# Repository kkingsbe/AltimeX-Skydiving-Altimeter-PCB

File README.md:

# AltimeX

This repo contains the PCB files for an open-source ColorAlti analog that I created, which can be made for about $30. Sadly, the programmer cable costs anywhere from $60-$120, however if you need yours programmed you can reach out to me and we can work something out (I have one).

This is still an active work in progress. A LiPo with a capacity of at least 250mAh should be fine since the current draw of the board is minimal. The CAD files for an enclosure that can fit in the audible pocket on helmets will be up soon once tested.

## Bill of Materials
|Part            |Part Number            |Price (per item)|Amount|Link|
|----------------|-----------------------|----------------|------|----|
|MCU             |STM32F103              |$6.66           |1     |[Click Here](https://www.digikey.com/en/products/detail/stmicroelectronics/STM32F103C8T6/1646338)|
|LED Strip       |WS2813B                |$15.00          |1     |[Click Here](https://www.amazon.com/LOAMLIN-Individually-Addressable-144Pixels-Waterproof/dp/B0BDRCQWWQ/ref=sr_1_30_sspa?crid=3CKX9YASAYWQJ&keywords=ws2813b%2Bled%2Bstrip%2Bhigh%2Bdensity&qid=1681772673&sprefix=ws2813b%2Bled%2Bstrip%2Bhigh%2Bdensity%2Caps%2C69&sr=8-30-spons&spLa=ZW5jcnlwdGVkUXVhbGlmaWVyPUEyUUZPR0xCU1BTRFlNJmVuY3J5cHRlZElkPUEwNDg5NDI1TTdWTUJPUDY0NUJGJmVuY3J5cHRlZEFkSWQ9QTAzMjEyNTgyOTUyUFVVTVlURDdKJndpZGdldE5hbWU9c3BfbXRmJmFjdGlvbj1jbGlja1JlZGlyZWN0JmRvTm90TG9nQ2xpY2s9dHJ1ZQ&th=1)|
|Boost Converter |RP400N501A-TR-FE       |$1.48           |1     |[Click Here](https://www.digikey.com/en/products/detail/nisshinbo-micro-devices-inc/RP400N501A-TR-FE/10244946?s=N4IgTCBcDaIE4AcAsAGFA7ArCgjAQxAF0BfIA)|
|Linear Regulator|LD1117S33TR            |$0.66           |1     |[Click Here](https://www.digikey.com/en/products/detail/stmicroelectronics/LD1117S33TR/585766?s=N4IgTCBcDaIDYBMCMKDsBnAzJgLgJxAF0BfIA)|
|Schottky Diode  |RSX101MM-30TFTR        |$0.45           |1     |[Click Here](https://www.digikey.com/en/products/detail/rohm-semiconductor/RSX101MM-30TFTR/9748173)|
|10uh Inductor   |ASPI-0630LR-100M-T15   |$0.83           |1     |[Click Here](https://www.digikey.com/en/products/detail/abracon-llc/ASPI-0630LR-100M-T15/3059602?s=N4IgTCBcDaIIYGcAOBLAtABgGwGYMBsAnNARgwwFsQBdAXyA)|
|10uF Capactior  |                       |$0.25           |3     |[Click Here](https://www.digikey.com/en/products/detail/murata-electronics/GRM21BR61E106KA73L/2334874)|
|4.7uF Capacitor |                       |$0.10           |1     |[Click Here](https://www.digikey.com/en/products/detail/samsung-electro-mechanics/CL21A475KAQNNNE/3886902)|
|100nF Capacitor |                       |$0.10           |7     |[Click Here](https://www.digikey.com/en/products/detail/yageo/CC0805KRX7R9BB104/302874)|
|JTAG Connector  |FTSH-105-01-H-DV-K-P-TR|$5.63           |1     |[Click Here](https://www.digikey.com/en/products/detail/samtec-inc./FTSH-105-01-H-DV-K-P-TR/9594223?utm_adgroup=Rectangular%20Connectors%20-%20Headers%2C%20Male%20Pins&utm_source=google&utm_medium=cpc&utm_campaign=Shopping_Product_Connectors%2C%20Interconnects_NEW&utm_term=&utm_content=Rectangular%20Connectors%20-%20Headers%2C%20Male%20Pins&gclid=Cj0KCQiAx6ugBhCcARIsAGNmMbh4-y1PB26lYnSIvQfyvOCW9n3EWnzOqesUZbafweeNy_JcrjvtJzoaAvwaEALw_wcB)|
|4.7k Resistor   |                       |$0.10           |2     |[Click Here](https://www.digikey.com/en/products/detail/yageo/RC0402JR-074K7L/726477)|
|500 ohm Resistor|                       |$2.64           |1     |[Click Here](https://www.digikey.com/en/products/detail/vishay-dale/TNPU0805500RAZEN00/6615940)|
|1M Resistor     |                       |$0.10           |1     |[Click Here](https://www.digikey.com/en/products/detail/yageo/RC0805FR-071ML/727445)|
|10MHz Resonator |                       |$0.24           |1     |[Click Here](https://www.digikey.com/en/products/detail/yageo/RC0805FR-071ML/727445)|
|SMD LED         |                       |$0.26           |1     |[Click Here](https://www.digikey.com/en/products/detail/liteon/LTST-C191KRKT/386837)|
|Micro USB Port  |                       |$0.46           |1     |[Click Here](https://www.digikey.com/en/products/detail/amphenol-cs-fci/10118193-0001LF/2785388)|
|Baro Sensor     |LPS22HBTR              |$2.13           |1     |[Click Here](https://www.digikey.com/en/products/detail/stmicroelectronics/LPS22HBTR/5799910)|

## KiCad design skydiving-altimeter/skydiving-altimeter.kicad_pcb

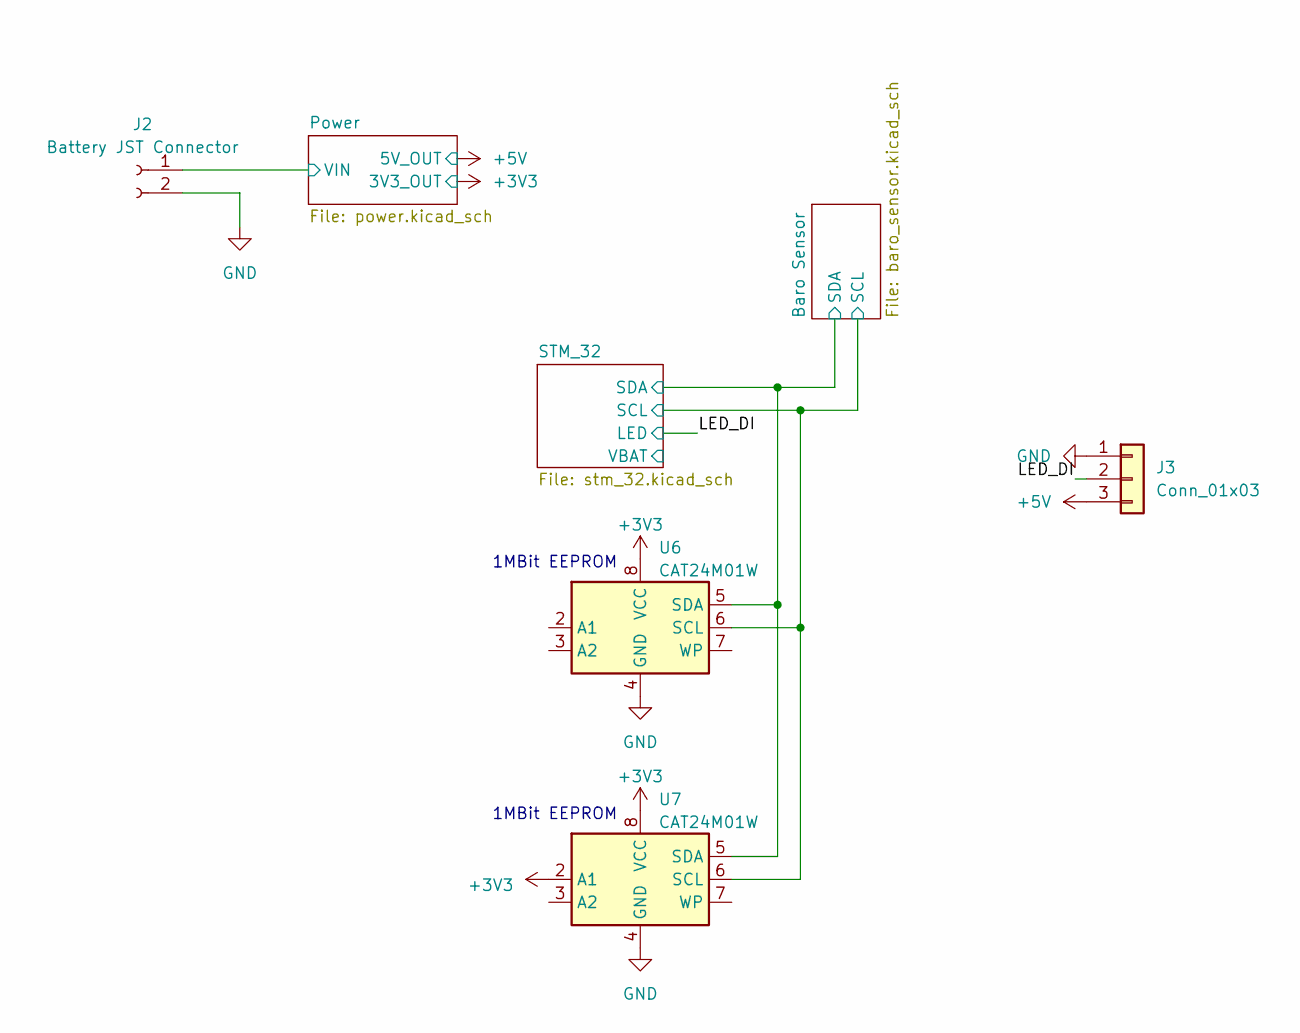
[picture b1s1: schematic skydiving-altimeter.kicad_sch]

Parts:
J2: Battery JST Connector; JST_S2B-PH-K-S(LF)(SN)
J3: Conn_01x03; PinHeader_1x03_P2.54mm_Vertical
U6, U7: CAT24M01W; SOIC-8_3.9x4.9mm_P1.27mm

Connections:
+3V3: U6.8 (VCC), U7.2 (A1), U7.8 (VCC); also elsewhere on the board
+5V: J3.3; also elsewhere on the board
/Baro Sensor/SCL: U6.6 (SCL), U7.6 (SCL); also elsewhere on the board
/Baro Sensor/SDA: U6.5 (SDA), U7.5 (SDA); also elsewhere on the board
/LED_DI: J3.2; also elsewhere on the board
/Power/VIN: J2.1; also elsewhere on the board
GND: J2.2, J3.1, U6.4 (GND), U7.4 (GND); also elsewhere on the board

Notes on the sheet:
1MBit EEPROM

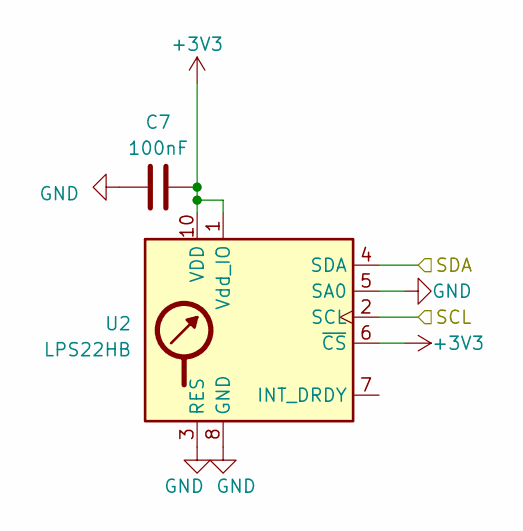
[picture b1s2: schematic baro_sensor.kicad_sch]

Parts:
C7: 100nF; C_0805_2012Metric
U2: LPS22HB; ST_HLGA-10_2x2mm_P0.5mm_LayoutBorder3x2y

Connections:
+3V3: C7.1, U2.1 (Vdd_IO), U2.6 (~CS), U2.10 (VDD); also elsewhere on the board
/Baro Sensor/SCL: U2.2 (SCL); also elsewhere on the board
/Baro Sensor/SDA: U2.4 (SDA); also elsewhere on the board
GND: C7.2, U2.3 (RES), U2.5 (SA0), U2.8 (GND), U2.9 (GND); also elsewhere on the board

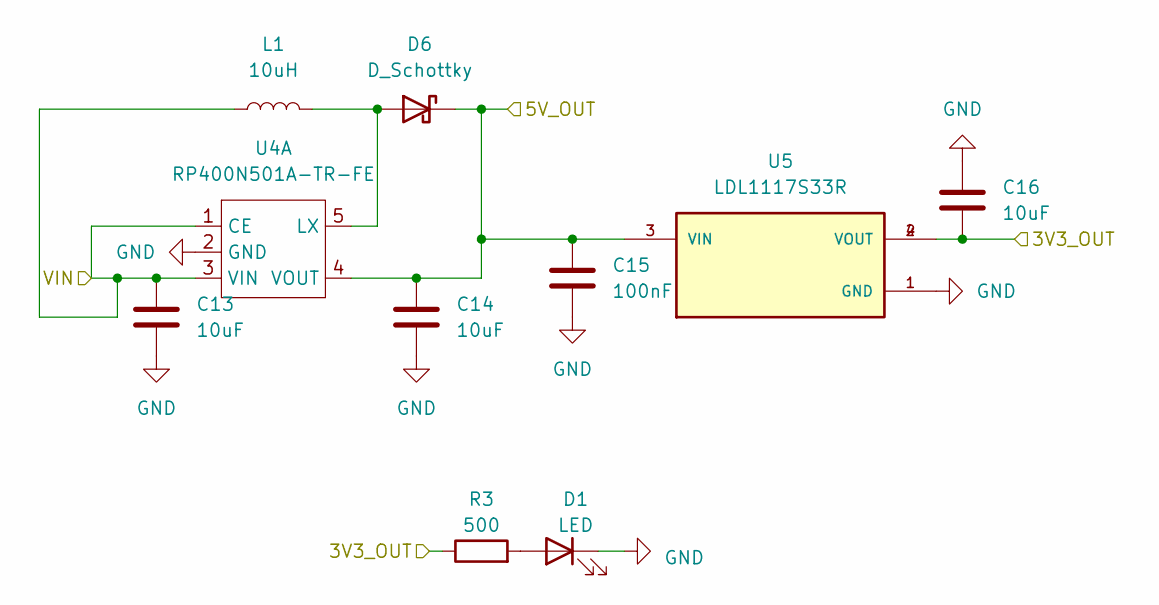
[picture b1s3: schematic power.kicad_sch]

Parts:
C13, C14, C16: 10uF; C_0805_2012Metric
C15: 100nF; C_0805_2012Metric
D1: LED; D_0603_1608Metric
D6: D_Schottky; D_SOD-123F
L1: 10uH; IND_ASPI-0630LR-100M-T15
R3: 500; R_0805_2012Metric
U4: RP400N501A-TR-FE; SOT-23-5
U5: LDL1117S33R; SOT-223; PARTREV 7

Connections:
+3V3: C16.2, R3.1, U5.2 (VOUT), U5.4 (VOUT); also elsewhere on the board
+5V: C14.1, C15.1, D6.1 (K), U4.4 (VOUT), U5.3 (VIN); also elsewhere on the board
/Power/VIN: C13.1, L1.1, U4.1 (CE), U4.3 (VIN); also elsewhere on the board
GND: C13.2, C14.2, C15.2, C16.1, D1.1 (K), U4.2 (GND), U5.1 (GND); also elsewhere on the board
unnamed: D1.2 (A), R3.2
unnamed: D6.2 (A), L1.2, U4.5 (LX)

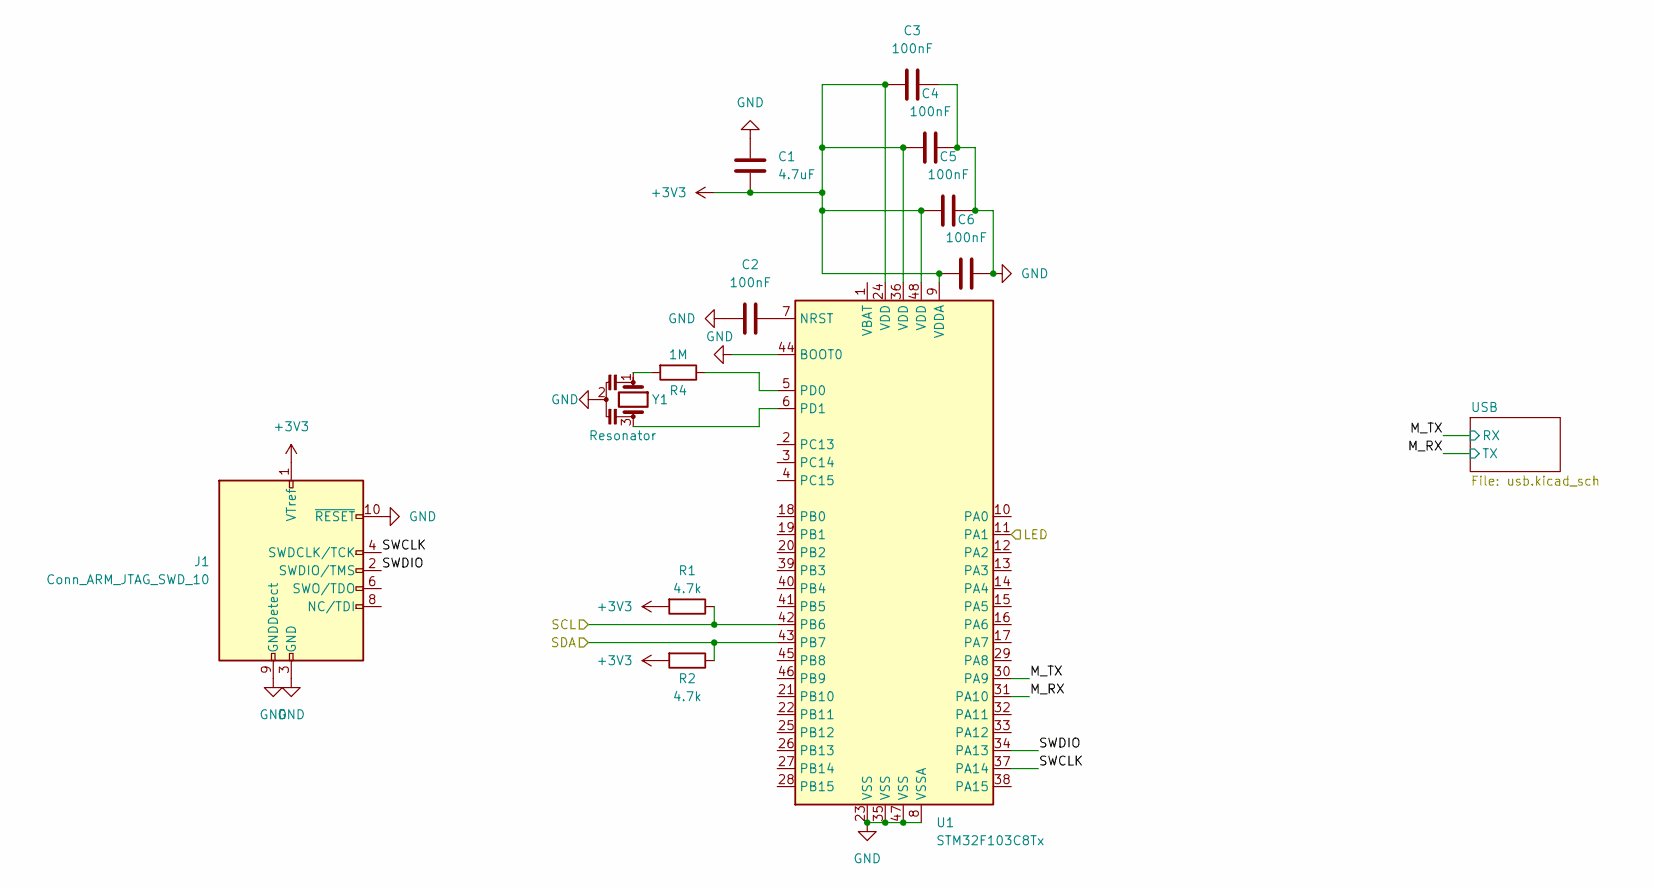
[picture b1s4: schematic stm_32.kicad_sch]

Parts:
C1: 4.7uF; C_0805_2012Metric
C2, C3, C4, C5, C6: 100nF; C_0805_2012Metric
J1: Conn_ARM_JTAG_SWD_10; PinHeader_2x05_P1.27mm_Vertical_SMD
R1, R2: 4.7k; R_0402_1005Metric
R4: 1M; R_0805_2012Metric
U1: STM32F103C8Tx; LQFP-48_7x7mm_P0.5mm
Y1: Resonator; JGC42-8828A_CSTNE10M0G550000R0

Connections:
+3V3: C1.2, C3.2, C4.2, C5.2, C6.2, J1.1 (VTref), R1.2, R2.2, U1.9 (VDDA), U1.24 (VDD), U1.36 (VDD), U1.48 (VDD); also elsewhere on the board
/Baro Sensor/SCL: R1.1, U1.42 (PB6); also elsewhere on the board
/Baro Sensor/SDA: R2.1, U1.43 (PB7); also elsewhere on the board
/LED_DI: U1.11 (PA1); also elsewhere on the board
/STM_32/M_RX: U1.31 (PA10); also elsewhere on the board
/STM_32/M_TX: U1.30 (PA9); also elsewhere on the board
/STM_32/SWCLK: J1.4 (SWDCLK/TCK), U1.37 (PA14)
/STM_32/SWDIO: J1.2 (SWDIO/TMS), U1.34 (PA13)
GND: C1.1, C2.2, C3.1, C4.1, C5.1, C6.1, J1.3 (GND), J1.5 (GND), J1.9 (GNDDetect), J1.10 (~RESET), U1.8 (VSSA), U1.23 (VSS), U1.35 (VSS), U1.44 (BOOT0), U1.47 (VSS), Y1.2; also elsewhere on the board
unnamed: R4.2, Y1.1
unnamed: C2.1, U1.7 (NRST)
unnamed: R4.1, U1.5 (PD0)
unnamed: U1.6 (PD1), Y1.3

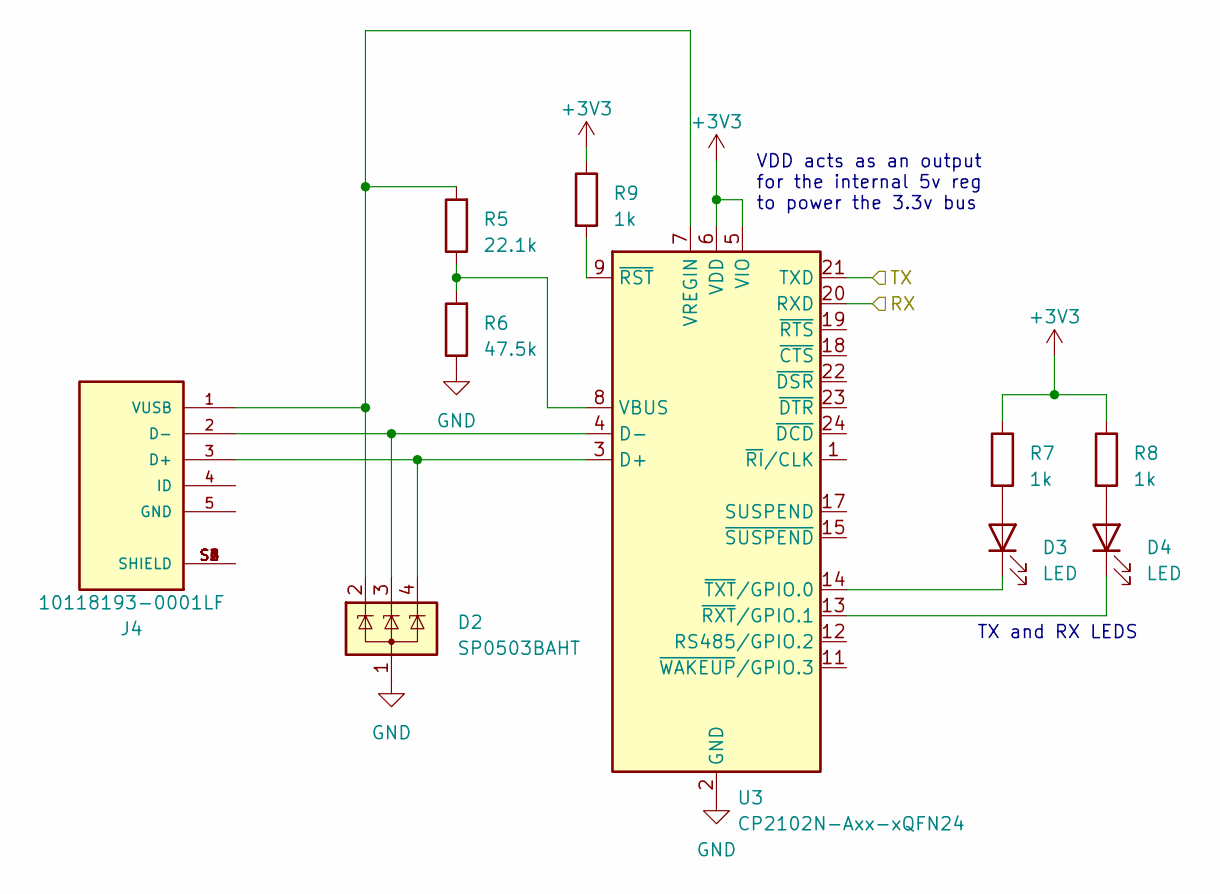
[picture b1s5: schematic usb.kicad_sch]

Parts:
D2: SP0503BAHT; SOT-143
D3, D4: LED; D_0603_1608Metric
J4: 10118193-0001LF; AMPHENOL_10118193-0001LF; PARTREV E
R5: 22.1k; R_0805_2012Metric
R6: 47.5k; R_0805_2012Metric
R7, R8, R9: 1k; R_0805_2012Metric
U3: CP2102N-Axx-xQFN24; QFN-24-1EP_4x4mm_P0.5mm_EP2.6x2.6mm

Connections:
+3V3: R7.1, R8.1, R9.1, U3.5 (VIO), U3.6 (VDD); also elsewhere on the board
/STM_32/M_RX: U3.21 (TXD); also elsewhere on the board
/STM_32/M_TX: U3.20 (RXD); also elsewhere on the board
GND: D2.1 (A), R6.1, U3.2 (GND), U3.25 (GND); also elsewhere on the board
unnamed: D3.2 (A), R7.2
unnamed: D3.1 (K), U3.14 (~TXT/GPIO.0)
unnamed: D4.2 (A), R8.2
unnamed: D4.1 (K), U3.13 (~RXT/GPIO.1)
unnamed 17: D2.4 (K), U3.3 (D+); also elsewhere on the board
unnamed 18: D2.3 (K), U3.4 (D-); also elsewhere on the board
unnamed 20: D2.2 (K), R5.2, U3.7 (VREGIN); also elsewhere on the board
unnamed: R5.1, R6.2, U3.8 (VBUS)
unnamed: R9.2, U3.9 (~RST)

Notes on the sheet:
TX and RX LEDS
VDD acts as an output for the internal 5v reg to power the 3.3v bus

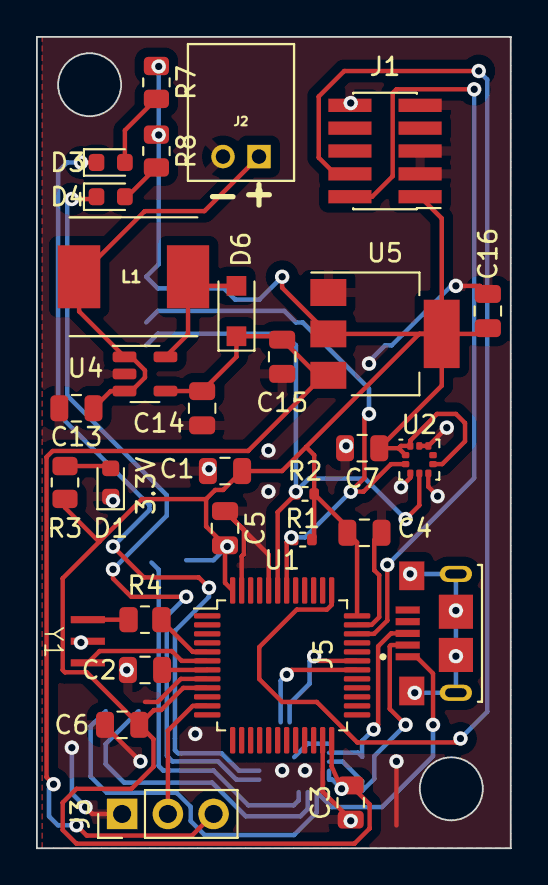
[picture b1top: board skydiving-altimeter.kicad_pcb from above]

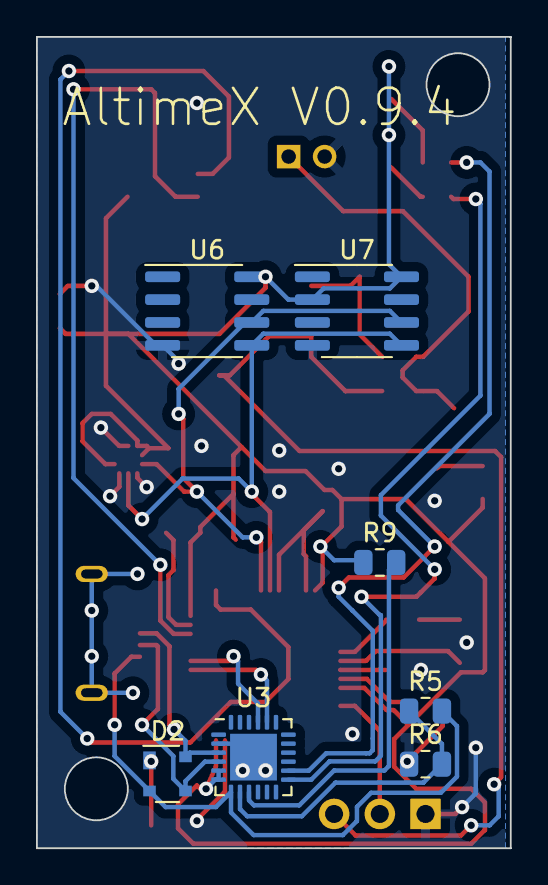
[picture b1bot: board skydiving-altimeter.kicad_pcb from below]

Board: 2 copper layers, 26.3 x 45.1 mm, 38 parts (7 on the bottom side), 27 nets.

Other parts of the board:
J5: 10118193-0001LF; AMPHENOL_10118193-0001LF

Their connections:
unnamed 17: J5.3 (D+); also elsewhere on the board
unnamed 18: J5.2 (D-); also elsewhere on the board
unnamed: J5.S1 (SHIELD), J5.S2 (SHIELD), J5.S3 (SHIELD), J5.S4 (SHIELD), J5.S5 (SHIELD), J5.S6 (SHIELD)
unnamed 20: J5.1 (VUSB); also elsewhere on the board

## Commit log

2023-04-17 Started rerouting
2023-04-18 Finished reroute
2023-04-27 First working version!
2023-06-01 Minor changes
2023-06-02 Began adding 10 ohm current limiting resistors
2023-06-02 Fixed CSB pin routing
2023-06-02 Switched most components to 0402
2023-06-28 Switched from the bmp to the lps. Added usb port
2023-06-29 Added external resonator to allow usb
2023-06-30 Finalize BOM
2023-06-30 Generated gerbers. Added version number to back
2023-07-14 Mostly rerouted
2023-09-04 Completed reroute
